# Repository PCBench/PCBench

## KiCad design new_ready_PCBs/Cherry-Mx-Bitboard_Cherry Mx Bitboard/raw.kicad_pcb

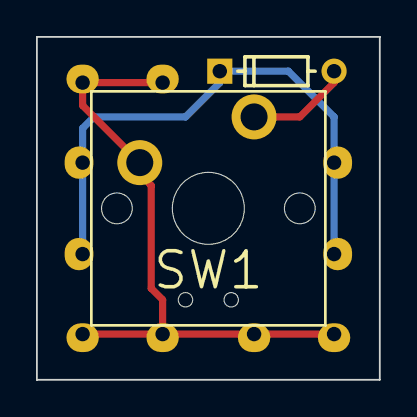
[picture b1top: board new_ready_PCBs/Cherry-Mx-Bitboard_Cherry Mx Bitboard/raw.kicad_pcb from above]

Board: 2 copper layers, 19.0 x 19.0 mm, 12 parts (1 on the bottom side), 3 nets.

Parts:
D1: D; diode
P11, P12, P13, P14, P15, P16, P21, P22, P23, P24: CONN_01X01; wirepad
SW1: SW_PUSH; switch

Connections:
/1: P11.1, P12.1, P13.1, P14.1, P15.1, P16.1, SW1.1
/2: D1.1, P21.1, P22.1, P23.1, P24.1
unnamed: D1.2, SW1.2

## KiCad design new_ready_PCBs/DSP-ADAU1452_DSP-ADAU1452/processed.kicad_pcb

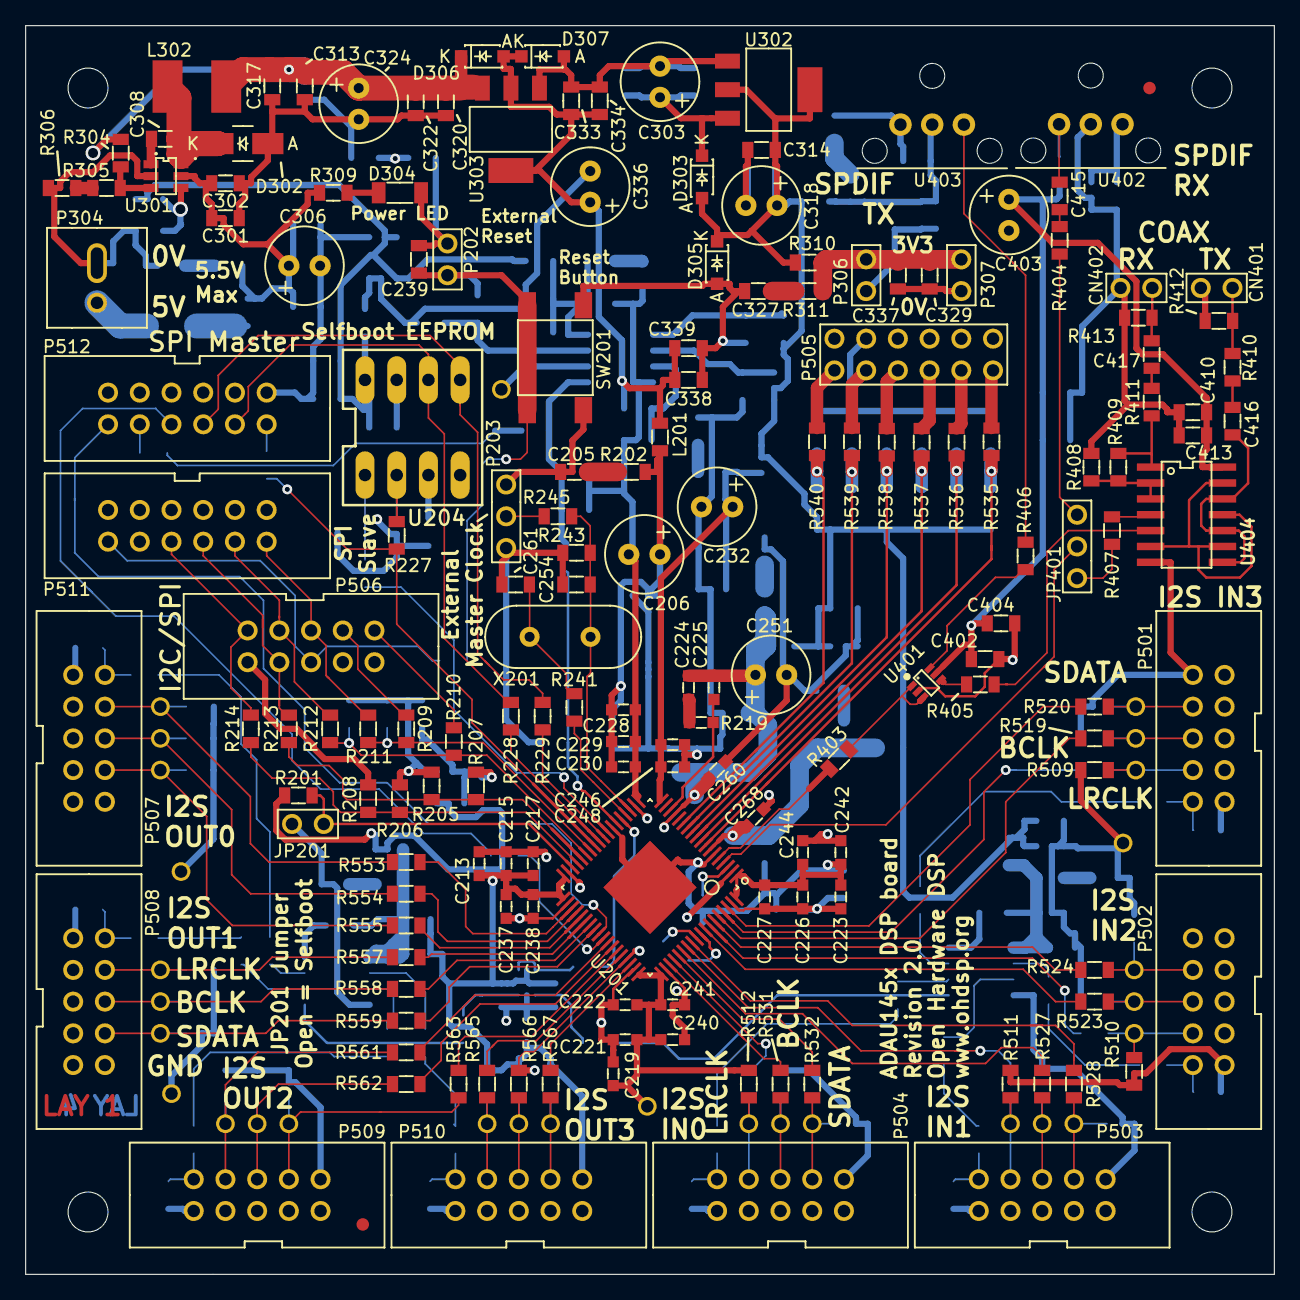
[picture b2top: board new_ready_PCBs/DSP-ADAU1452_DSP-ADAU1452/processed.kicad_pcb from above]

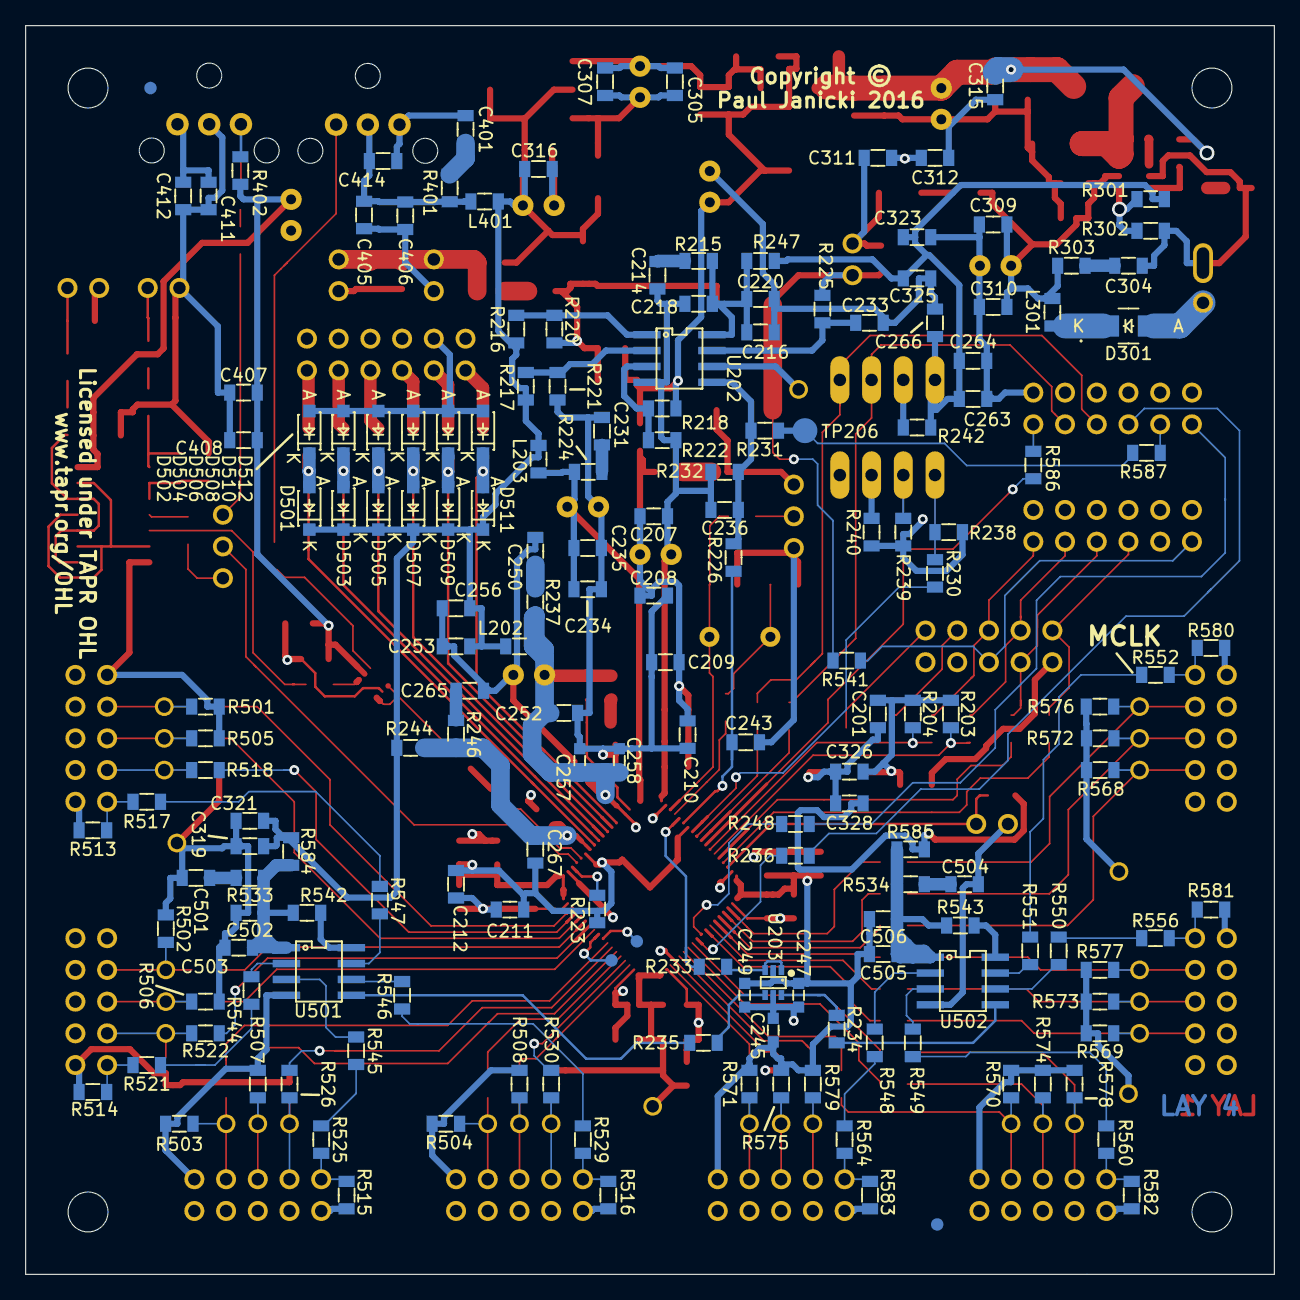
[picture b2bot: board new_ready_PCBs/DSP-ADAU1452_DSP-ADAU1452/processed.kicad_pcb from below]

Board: 4 copper layers, 100.0 x 100.0 mm, 377 parts (177 on the bottom side), 190 nets.

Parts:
C201, C208, C210, C212, C218, C233, C235, C236, C239, C243, C253, C264, C302, C307, C310, C314, C317, C319, C320, C323, C326, C329, C333, C338, C402, C406, C412, C413, C414, C416, C417, C503, C506: 100n; SMD-0805
C205, C214, C231, C250, C265, C304, C327, C401, C501, C504: 100p; SMD-0805
C206, C232, C251, C303, C306, C318, C324, C336, C403: 220u; CAP-TH-D6.3mmP2.5mm
C207, C234, C252, C267, C301, C305, C309, C313, C315, C316, C322, C334, C405, C502, C505: 22u; SMD-0805
C209, C211, C216, C256, C266, C321, C325, C328, C337, C339, C404, C410, C411: 10u; SMD-0805
C213, C219, C223, C228, C237, C240, C242, C245, C246, C257: 1u; SMD-0603
C215, C221, C226, C229, C238, C241, C244, C247, C248, C258, C268: 100n; SMD-0603
C217, C222, C227, C230, C249, C260: 10n; SMD-0603
C220, C263, C308, C415: 10n; SMD-0805
C224: 5n6; SMD-0603
C225: 150p; SMD-0603
C254, C261: 33p; SMD-0805
C311, C312, C407, C408: N/F; SMD-0805
CN401, CN402: COAX; CONN_SIL_2_1MM
D301, D302: B240A; DIODE-SMA
D303, D305, D306, D307, D501, D502, D503, D504, D505, D506, D507, D508, D509, D510, D511, D512: SS14L; DIODE-SOD-123
D304: Green LED 1206; SMD-1206
FID1, FID2, FID3, FID4: MNT_HOLE; FID-1MM-3MM
JP201: CONN_2x1; CONN_SIL_2_1MM
JP401: CONN_3x1; CONN_SIL_3_1MM
L201, L202, L203, L301, L401: 600R@100MHz; SMD-0805
L302: TYS50404R7N-10; IND-TYS5040-HS
MNT301, MNT302, MNT303, MNT304: MNT_HOLE; MNT_HOLE_3.2mm
P202, P306, P307: CONN_2x1; CONN_SIL_2_1MM
P203: CONN_3x1; CONN_SIL_3_1MM
P304: CONN_2x1; CONN-2WAY-2.54mm-3.81mm-SPACING
P501, P502, P503, P504, P506, P507, P508, P509, P510: CONN_02X05; CONN_DIL_2X5_BOX_1MM
P505: CONN_02X06; CONN_DIL_2X6_1MM
P511, P512: CONN_02X06; CONN_DIL_2X6_BOX_1MM
R201, R225, R542, R543: 1k; SMD-0805
R202, R215, R224, R237, R246, R303, R311, R401, R533, R534: 47; SMD-0805
R203, R204, R205, R206, R207, R208, R209, R210, R220, R239, R243, R245, R501, R502, R503, R504, R505, R506, R507, R508, R509, R510, R511, R512, R513, R514, R515, R516, R568, R569, R570, R571, R572, R573, R574, R575, R576, R577, R578, R579, R580, R581, R582, R583: N/F; SMD-0805
R211, R227, R228, R229, R230, R233, R234, R235, R236, R248, R403, R404, R405, R406, R407, R413, R544, R545, R546, R547, R548, R549, R550, R551, R553, R554, R555, R557, R558, R559, R561, R562, R563, R565, R566, R567: 75; SMD-0805
R212, R213, R214, R216, R223, R306, R517, R518, R519, R520, R521, R522, R523, R524, R525, R526, R527, R528, R529, R530, R531, R532, R541, R552, R556, R560, R564, R586, R587: 0; SMD-0805
R217: 12k; SMD-0805
R218: 3k3; SMD-0805
R219: 4k3; SMD-0603
R221: 3k; SMD-0805
R222: 3k6; SMD-0805
R226, R231, R241, R411: 100; SMD-0805
R232: 100k; SMD-0805
R238, R240, R242, R302, R402, R408, R409: 10k; SMD-0805
R244, R247, R310, R584, R585: 1; SMD-0805
R301: 16k; SMD-0805
R304: 24k; SMD-0805
R305: 15k; SMD-0805
R309: 470; SMD-0805
R410: 360; SMD-0805
R412: 91; SMD-0805
R535, R536, R537, R538, R539, R540: 4k7; SMD-0805
SW201: SWITCH; SW_TACT_SMD
TP201, TP501, TP502, TP503, TP504, TP505, TP506, TP507, TP508, TP509, TP510, TP511, TP512, TP513, TP514, TP515, TP516, TP517, TP518, TP519, TP520, TP521, TP522, TP523, TP524, TP525, TP526, TP527, TP528: PIN; TP-TH-1mm
TP204, TP205: PIN; TP-1mm
TP206: PIN; TP-2mm
U201: ADAU1452WBCPZ; IC-LFCSP72-HANDFIT
U202: ADM13307-5ARZ; IC_SOIC_8
U203: NC7WZ17P6X; IC-SC70-6
U204: 25AA1024; IC_DIP_8
U301: ADP2301AUJZ; IC-SOT23-6
U302: TLV1117LV33DCY; IC-SOT-223
U303: TLV1117LV12DCY; IC-SOT-223
U401: NC7WZ16P6X; IC-SC70-6
U402: IC-SPDIF-RX-OPTO; IC_SPDIF_OPTO
U403: IC-SPDIF-TX-OPTO; IC_SPDIF_OPTO
U404: 74HC04; IC_SOIC_14
U501, U502: NB3L553; IC_SOIC_8
X201: 24M576; XTAL_HC49_TH

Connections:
/ADAU1452/ADAU_SPDIF_RX: JP401.2, U201.4
/ADAU1452/ADAU_SPDIF_TX: R403.2, U201.5
/ADAU1452/ADCIN_BCLK0: R531.2, U201.57
/ADAU1452/ADCIN_BCLK1: R527.2, U201.60
/ADAU1452/ADCIN_BCLK2: R523.2, U201.65
/ADAU1452/ADCIN_BCLK3: R519.2, U201.68
/ADAU1452/ADCIN_LRCLK0: R530.2, U201.58
/ADAU1452/ADCIN_LRCLK1: R526.2, U201.61
/ADAU1452/ADCIN_LRCLK2: R522.2, U201.66
/ADAU1452/ADCIN_LRCLK3: R518.2, U201.69
/ADAU1452/ADCIN_SDATA0: R532.2, U201.59
/ADAU1452/ADCIN_SDATA1: R528.2, U201.62
/ADAU1452/ADCIN_SDATA2: R524.2, U201.67
/ADAU1452/ADCIN_SDATA3: R520.2, U201.70
/ADAU1452/AVDD: C267.1, C268.1, R244.1, R246.1, U201.7
/ADAU1452/DACOUT_BCLK0: R554.1, U201.40
/ADAU1452/DACOUT_BCLK1: R558.1, U201.43
/ADAU1452/DACOUT_BCLK2: R562.1, U201.48
/ADAU1452/DACOUT_BCLK3: R566.1, U201.51
/ADAU1452/DACOUT_LRCLK0: R553.1, U201.39
/ADAU1452/DACOUT_LRCLK1: R557.1, U201.42
/ADAU1452/DACOUT_LRCLK2: R561.1, U201.47
/ADAU1452/DACOUT_LRCLK3: R565.1, U201.50
/ADAU1452/DACOUT_SDATA0: R555.1, U201.41
/ADAU1452/DACOUT_SDATA1: R559.1, U201.44
/ADAU1452/DACOUT_SDATA2: R563.1, U201.49
/ADAU1452/DACOUT_SDATA3: R567.1, U201.52
/ADAU1452/DSP_RESET: C243.1, R226.1, U201.24
/ADAU1452/DVDD: C206.1, C207.1, C208.1, C209.1, C210.1, C211.1, C212.1, C213.1, C215.1, C217.1, C219.1, C221.1, C222.1, C223.1, C226.1, C227.1, C228.1, C229.1, C230.1, L201.2, R202.1, U201.20, U201.35, U201.53, U201.71
/ADAU1452/GLB_RESET: R231.1, R587.2, TP206.1
/ADAU1452/I2C_SCL: P506.1, R210.1
/ADAU1452/I2C_SDA: P506.3, R209.1
/ADAU1452/IOVDD: C232.1, C234.1, C235.1, C237.1, C238.1, C240.1, C241.1, C242.1, C244.1, C245.1, C246.1, C247.1, C248.1, C249.1, L203.2, R224.1, U201.2, U201.18, U201.38, U201.56, U203.5
/ADAU1452/MAN_RST_IN: C239.1, P202.1, R225.2, R541.2, SW201.1
/ADAU1452/MCLK: R235.1, U501.5
/ADAU1452/MCLK2: R234.1, U502.5
/ADAU1452/MCLK_ADAU: R233.2, U201.23
/ADAU1452/MISO/SDA: R204.2, R209.2, R211.2, U201.30
/ADAU1452/MOSI/ADDR1: R205.2, R207.2, R213.2, U201.32
/ADAU1452/M_SS: R230.2, R238.2, U204.1
/ADAU1452/PVDD: C224.1, C225.1, C251.1, C252.1, C257.1, C258.1, C260.1, L202.2, R237.1, U201.15
/ADAU1452/SCLK/SCL: R203.2, R210.2, R212.2, U201.31
/ADAU1452/SELFBOOT: JP201.1, R201.2, U201.34
/ADAU1452/SPI_MISO: P506.5, P511.2, R211.1
/ADAU1452/SPI_MOSI: P506.8, P511.6, R213.1
/ADAU1452/SPI_SCLK: P506.7, P511.4, R212.1
/ADAU1452/SPI_SS: P506.9, P511.8, R214.1
/ADAU1452/SS/ADDR0: R206.2, R208.2, R214.2, U201.33
/ADAU1452/XTALIN: C254.1, R243.1, R245.1, U201.21, X201.1
/ADAU1452/XTALOUT: R241.1, U201.22
/Connectors/AUXADCIN_1: D501.1, D502.2, R535.2, U201.8
/Connectors/AUXADCIN_2: D503.1, D504.2, R536.2, U201.9
/Connectors/AUXADCIN_3: D505.1, D506.2, R537.2, U201.10
/Connectors/AUXADCIN_4: D507.1, D508.2, R538.2, U201.11
/Connectors/AUXADCIN_5: D509.1, D510.2, R539.2, U201.12
/Connectors/AUXADCIN_6: D511.1, D512.2, R540.2, U201.13
/Connectors/I2C_RST: P506.6, P511.12, R541.1
/Connectors/MCLKA1: R529.2, R546.1
/Connectors/MCLKA2: R525.2, R545.1
/Connectors/MCLKA3: R521.2, R544.1
/Connectors/MCLKA4: R517.2, R547.1
/Connectors/MCLKB1: R551.1, R552.1
/Connectors/MCLKB2: R550.1, R556.1
/Connectors/MCLKB3: R549.1, R560.1
/Connectors/MCLKB4: R548.1, R564.1
/Connectors/M_MUTE: P512.12, R248.2
/Connectors/M_SPI_MISO: R227.1, R586.2, U201.29
/Connectors/M_SPI_MOSI: P512.6, R229.2, U204.5
/Connectors/M_SPI_SCLK: P512.4, R228.2, U204.6
/Connectors/M_SPI_SS: P512.8, R236.2
/Power Supply/2V1: C313.1, C315.1, C317.1, C320.1, C322.1, C324.1, D306.2, L302.2, R304.2, U303.3
GNDD: C201.2, C205.2, C206.2, C207.2, C208.2, C209.2, C210.2, C211.2, C212.2, C213.2, C214.2, C215.2, C216.2, C217.2, C218.2, C219.2, C220.2, C221.2, C222.2, C223.2, C226.2, C227.2, C228.2, C229.2, C230.2, C231.2, C232.2, C233.2, C234.2, C235.2, C236.2, C237.2, C238.2, C239.2, C240.2, C241.2, C242.2, C243.2, C244.2, C245.2, C246.2, C247.2, C248.2, C249.2, C250.2, C251.2, C252.2, C253.2, C254.2, C256.2, C257.2, C258.2, C260.2, C261.2, C263.2, C264.2, C265.2, C266.2, C267.2, C268.2, C301.1, C302.1, C303.2, C304.2, C305.2, C306.2, C307.2, C309.1, C310.1, C311.1, C312.1, C313.2, C314.2, C315.2, C316.2, C317.2, C318.2, C319.2, C320.2, C321.2, C322.2, C323.2, C324.2, C325.2, C326.2, C327.2, C328.2, C329.2, C333.2, C334.2, C336.2, C337.2, C338.2, C339.2, C401.2, C402.2, C403.2, C404.2, C405.2, C406.2, C407.2, C408.2, C410.2, C411.2, C412.2, C413.2, C414.2, C501.2, C502.2, C503.2, C504.2, C505.2, C506.2, CN401.2, CN402.2, D302.1, D304.2, D305.1, D307.1, D502.1, D504.1, D506.1, D508.1, D510.1, D512.1, JP201.2, P202.2, P203.1, P203.3, P304.2, P306.2, P307.2, P501.1, P501.3, P501.5, P501.7, P501.9, P501.10, P502.1, P502.3, P502.5, P502.7, P502.9, P502.10, P503.1, P503.3, P503.5, P503.7, P503.9, P503.10, P504.1, P504.3, P504.5, P504.7, P504.9, P504.10, P505.1, P505.3, P505.5, P505.7, P505.9, P505.11, P506.10, P507.1, P507.3, P507.5, P507.7, P507.9, P507.10, P508.1, P508.3, P508.5, P508.7, P508.9, P508.10, P509.1, P509.3, P509.5, P509.7, P509.9, P509.10, P510.1, P510.3, P510.5, P510.7, P510.9, P510.10, P511.1, P511.3, P511.5, P511.7, P511.9, P511.11, P512.1, P512.3, P512.5, P512.7, P512.9, P512.11, R207.1, R208.1, R220.1, R221.1, R222.1, R223.1, R232.1, R243.2, R302.1, R306.1, R408.1, R412.1, R413.1, R501.1, R502.1, R503.1, R504.1, R505.1, R506.1, R507.1, R508.1, R509.1, R510.1, R511.1, R512.1, R513.1, R514.1, R515.1, R516.1, R568.1, R569.1, R570.1, R571.1, R572.1, R573.1, R574.1, R575.1, R576.1, R577.1, R578.1, R579.1, R580.1, R581.1, R582.1, R583.1, SW201.2, TP513.1, TP514.1, TP515.1, TP516.1, U201.1, U201.6, U201.19, U201.25, U201.36, U201.37, U201.54, U201.55, U201.72, U201.EP1, U202.4, U203.2, U204.4, U301.2, U302.1, U303.1, U401.2, U402.2, U403.3, U404.7, U501.4, U502.4
unnamed: C205.1, R202.2
unnamed: C214.1, R215.2
unnamed: C216.1, C218.1, C220.1, R215.1, R247.1, U202.8
unnamed: C224.2, R219.1
unnamed: C225.2, R219.2, U201.16
unnamed: C231.1, R224.2
unnamed: C233.1, R225.1, U202.7
unnamed: C236.1, R226.2, R231.2, R232.2, U202.5
unnamed: C250.1, R237.2
unnamed: C261.1, R241.2, X201.2
unnamed: C265.1, R246.2
unnamed: C304.1, R303.2
unnamed: C308.1, U301.1
unnamed: C308.2, D302.2, L302.1, U301.6
unnamed: C327.1, R311.2
unnamed: C329.1, C337.1, P306.1, P307.1, R310.1, R311.1
unnamed: C401.1, R401.2
unnamed: C402.1, C403.1, C404.1, C405.1, C406.1, C407.1, C408.1, C410.1, C411.1, C412.1, C413.1, C414.1, L401.2, R401.1, R402.1, U401.5, U402.1, U403.2, U404.14
unnamed: C415.1, R404.2
unnamed: C415.2, R402.2, U402.3
unnamed: C416.1, R410.2
unnamed: C416.2, U404.8, U404.10, U404.12
unnamed: C417.1, R411.2
unnamed: C417.2, CN402.1, R413.2
unnamed: C501.1, R533.2
unnamed: C502.1, C503.1, R533.1, R542.2, R584.2, U501.1
unnamed: C504.1, R534.2
unnamed: C505.1, C506.1, R534.1, R543.2, R585.2, U502.1
unnamed: CN401.1, R410.1, R412.2
unnamed: D301.1, P304.1
unnamed: D301.2, L301.1
unnamed: D304.1, R309.2
unnamed: JP401.1, R404.1
unnamed: JP401.3, R407.2
unnamed: P203.2, R245.2
unnamed: P501.2, R513.2, R517.1
unnamed: P501.4, R509.2, R518.1, TP501.1
unnamed: P501.6, R505.2, R519.1, TP505.1
unnamed: P501.8, R501.2, R520.1, TP506.1
unnamed: P502.2, R514.2, R521.1
unnamed: P502.4, R510.2, R522.1, TP502.1
unnamed: P502.6, R506.2, R523.1, TP507.1
unnamed: P502.8, R502.2, R524.1, TP508.1
unnamed: P503.2, R515.2, R525.1
unnamed: P503.4, R511.2, R526.1, TP503.1
unnamed: P503.6, R507.2, R527.1, TP509.1
unnamed: P503.8, R503.2, R528.1, TP510.1
unnamed: P504.2, R516.2, R529.1
unnamed: P504.4, R512.2, R530.1, TP504.1
unnamed: P504.6, R508.2, R531.1, TP511.1
unnamed: P504.8, R504.2, R532.1, TP512.1
unnamed: P505.2, R535.1
unnamed: P505.4, R536.1
unnamed: P505.6, R537.1
unnamed: P505.8, R538.1
unnamed: P505.10, R539.1
unnamed: P505.12, R540.1
unnamed: P507.2, R552.2, R580.2
unnamed: P507.4, R553.2, R576.2, TP517.1
unnamed: P507.6, R554.2, R572.2, TP521.1
unnamed: P507.8, R555.2, R568.2, TP522.1
unnamed: P508.2, R556.2, R581.2
unnamed: P508.4, R557.2, R577.2, TP518.1
unnamed: P508.6, R558.2, R573.2, TP523.1
unnamed: P508.8, R559.2, R569.2, TP524.1
unnamed: P509.2, R560.2, R582.2
unnamed: P509.4, R561.2, R578.2, TP519.1
unnamed: P509.6, R562.2, R574.2, TP525.1
unnamed: P509.8, R563.2, R570.2, TP526.1
unnamed: P510.2, R564.2, R583.2
unnamed: P510.4, R565.2, R579.2, TP520.1
unnamed: P510.6, R566.2, R575.2, TP527.1
unnamed: P510.8, R567.2, R571.2, TP528.1
unnamed: P512.2, R586.1
unnamed: P512.10, R587.1
unnamed: R216.2, R220.2, U202.1
unnamed: R217.2, R221.2, U202.2
unnamed: R218.2, R222.2, U202.3
unnamed: R223.2, U201.3
unnamed: R227.2, R239.2, U204.2
unnamed: R228.1, U201.28
unnamed: R229.1, U201.27
unnamed: R230.1, U201.26
unnamed: R233.1, U203.1, U203.3
unnamed: R234.2, U203.6
unnamed: R235.2, U203.4
unnamed: R236.1, U201.46
unnamed: R240.2, U204.3
unnamed: R242.2, U204.7
unnamed: R248.1, U201.45
unnamed: R301.1, R302.2, U301.4
unnamed: R304.1, R305.2, U301.3
unnamed: R305.1, R306.2
unnamed: R403.1, U401.1, U401.3
unnamed: R405.1, U404.5
unnamed: R405.2, U401.4
unnamed: R406.1, U401.6
unnamed: R406.2, U403.1
unnamed: R407.1, U404.4
unnamed: R408.2, R409.1, U404.2, U404.3
unnamed: R409.2, R411.1, U404.1
unnamed: R542.1, U501.8
unnamed: R543.1, U502.8
unnamed: R544.2, U501.2
unnamed: R545.2, U501.3
unnamed: R546.2, U501.6
unnamed: R547.2, U501.7
unnamed: R548.2, U502.2
unnamed: R549.2, U502.3
unnamed: R550.2, U502.6
unnamed: R551.2, U502.7
unnamed: TP201.1, U202.6
unnamed: TP204.1, U201.64
unnamed: TP205.1, U201.63
unnamed: U404.6, U404.9, U404.11, U404.13
VAA: C201.1, C253.1, C256.1, C263.1, C264.1, C266.1, C314.1, C316.1, C318.1, C319.1, C321.1, C323.1, C325.1, C326.1, C328.1, D303.1, D305.2, D501.2, D503.2, D505.2, D507.2, D509.2, D511.2, L202.1, L203.1, L401.1, R201.1, R203.1, R204.1, R205.1, R206.1, R216.1, R217.1, R238.1, R239.1, R240.1, R242.1, R244.2, R247.2, R301.2, R310.2, R584.1, R585.1, U204.8, U302.2
VCC: C301.2, C302.2, C303.1, C305.1, C306.1, C307.1, C309.2, C310.2, C311.2, C312.2, D303.2, L301.2, R303.1, R309.1, U301.5, U302.3
VDD: C333.1, C334.1, C336.1, C338.1, C339.1, D306.1, D307.2, L201.1, R218.1, U303.2

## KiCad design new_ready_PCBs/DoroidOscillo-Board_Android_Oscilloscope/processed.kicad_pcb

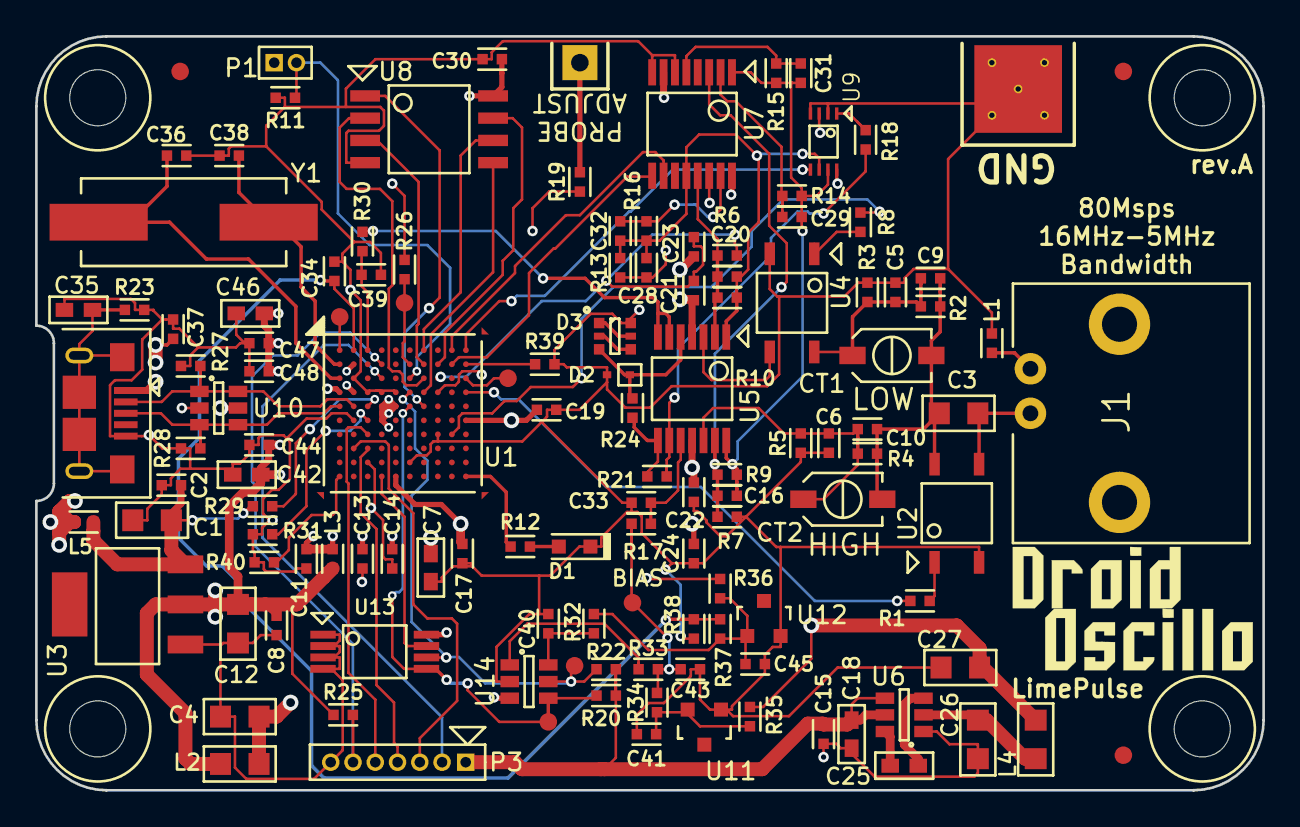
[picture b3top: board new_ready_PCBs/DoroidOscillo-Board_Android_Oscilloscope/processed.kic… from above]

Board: 4 copper layers, 70.0 x 43.0 mm, 132 parts (0 on the bottom side), 77 nets.

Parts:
C1, C4, C12, C26, C27: 22u 6.3V; SMD2012
C2, C8, C11, C14, C15, C17, C19, C23, C24, C30, C33, C37, C41, C43, C44, C45, C47: 0.1u; SMD1005
C3: 47n 100V; SMD2012
C5, C32: 4.7p; SMD1005
C6: 120p; SMD1005
C7, C18, C42, C46: 10u 6.3V; SMD1608
C9, C10, C39: NM; SMD1005
C13, C48: 22n; SMD1005
C16, C20: 2.2p; SMD1005
C21, C22, C34, C40: 1u; SMD1005
C25: 4.7u 6.3V; SMD1608
C28: 15p; SMD1005
C29: 3.3p; SMD1005
C31: 10p; SMD1005
C35: 4.7n 100V; SMD1608
C36, C38: 18p; SMD1005
CT1: TZC3R100A110 3p-10p; MURATA_TZC3
CT2: TZC3Z030A110R00 1.4p-3p; MURATA_TZC3
D1: APT1608EC; SMD1608_DIODE
D2: RB521S30T5G; SOD-523
D3: BAS16VY; SOT-363
FID1: Fiducial_C; Fiducial_1mm
FID2: Fiducial_A; Fiducial_1mm
FID3: Fiducial_B; Fiducial_1mm
HOLE3MM_NC, HOLE3MM_NC_2, HOLE3MM_NC_3, HOLE3MM_NC_4: VAL**; HOLE3MM_NC
J1: BNC; BNC-R
L1, L5: BLM15AG121SN1; SMD1005
L2, L4: LBR2012T202K; SMD2012
L3: BLM15AG601SN1; SMD1005
P1: USB_BOOT; PIN_HEADER_2_1.27mm
P2: FCI_10118193-0001LF; 10118193-0001LF
P3: JTAG; PIN_HEADER_7_1.27pitch
R1, R8, R11, R36, R39, R40: 2.2k 5%; SMD1005
R2: 1100k 1%; SMD1005
R3: 910k 1%; SMD1005
R4: 1.96M 1%; SMD1005
R5: 36k 1%; SMD1005
R6, R7: 3k 1%; SMD1005
R9, R10: 27k 1%; SMD1005
R12: 10k 5%; SMD1005
R13: 3.3k 1%; SMD1005
R14: 22k 1%; SMD1005
R15: 5.6k 1%; SMD1005
R16: 13.3k 1%; SMD1005
R17, R32: 4.7k 5%; SMD1005
R18: 910 1%; SMD1005
R19, R29: 100 5%; SMD1005
R20, R22, R25, R26: 4.7k; SMD1005
R21: 1k 1%; SMD1005
R23, R27, R28: 1M 5%; SMD1005
R24: 680 1%; SMD1005
R30: 0; SMD1005
R31: 12k 1%; SMD1005
R33: 2k 1%; SMD1005
R34: 8.2k 1%; SMD1005
R35, R38: 1.5k 1%; SMD1005
R37: 2.2k 1%; SMD1005
TP1: SCL; TestPad
TP2: SDA; TestPad
TP3: RST; TestPad
U1: LPC4370FET100; TFBGA100_MYREFLOW
U2, U4: CPC1017N
U3: AMS1117-3.3; SOT-223
U5: OPA4354AIPWR; TSSOP-14_4.4x5mm_Pitch0.65mm
U6: LM2664; SOT-23-6
U7: 74HC4052PW; TSSOP-16_4.4x5mm_Pitch0.65mm
U8: W25Q80BVSSIG; SOIJ-8_5.3x5.3mm_Pitch1.27mm
U9: TC7W53FK; SSOP8_P0.5W2.3
U10: USBLC6-2SC6; SOT-23-6
U11, U12: LM385M3-1.2/NOPB; SOT-23
U13: AT24C02C-XHM-T; TSSOP-8_4.4x3mm_Pitch0.65mm
U14: MCP4726A0T-E/CH; SOT-23-6
W1: ISP; TestPad
W2: PROBE_COMP_HOLE
W3: ADC1; TestPad
W4: PROBE_GND_PAD; Probe-ADJ-GND
W5: TP_BIAS; TestPad
Y1: ABLS-12.000MHZ-B4-T; Crystal_HC49-SD_SMD

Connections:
/USB_D+: P2.3, R28.1, U1.E1, U10.3, U10.4
/USB_D-: P2.2, R27.1, U1.E2, U10.1, U10.6
/USB_VBUS: R29.1, U1.E3
ADCHS_VNEG: C39.1, R30.2, U1.A3
ADCHS_VPOS0: C34.1, R37.2, R38.1, U1.A2
BIAS: C43.2, R17.1, R33.2, R34.1, W5.1
BOOT1: R40.1, U1.K1
BOOT2: P1.2, R11.1, U1.C6
BOOT3: R39.1, U1.B10
BOOT_ISP: U1.C10, W1.1
DAC_OUT: R33.1, U14.1
DAC_VREF: C45.1, R32.1, R36.2, R37.1, U12.1
DC_SW: R1.1, U1.D10
EEPROM_WP: U1.K4, U13.7
GND: C1.2, C2.2, C4.2, C5.2, C6.2, C7.2, C8.2, C11.2, C12.2, C13.2, C14.2, C15.2, C17.2, C18.2, C19.2, C21.2, C22.1, C23.2, C24.1, C26.2, C27.2, C30.2, C33.2, C34.2, C35.2, C36.1, C37.2, C38.1, C39.2, C40.1, C41.2, C42.2, C43.1, C44.2, C45.2, C46.2, C47.2, C48.2, D1.1, D2.2, D3.6, L1.2, P2.5, P3.7, R3.1, R5.2, R6.2, R7.2, R11.2, R23.2, R27.2, R28.2, R31.2, R38.2, R39.2, R40.2, U1.C2, U1.C8, U1.D3, U1.D4, U1.D5, U1.F2, U1.G8, U1.J3, U1.J6, U2.2, U3.1, U4.2, U6.1, U7.6, U7.8, U8.4, U9.2, U9.4, U10.2, U11.1, U12.2, U13.1, U13.2, U13.3, U13.4, U14.2, W4.1
I2C_SCL: R22.2, TP1.1, U1.D6, U13.6, U14.5
I2C_SDA: R20.2, TP2.1, U1.E6, U13.5, U14.4
JTAG_RESET: P3.6, R25.2, U1.B4
JTAG_TCK: P3.3, U1.H2
JTAG_TDI: P3.5, U1.G3
JTAG_TDO: P3.4, U1.H3
JTAG_TMS: P3.2, U1.C4
LED0: R12.1, U1.K10
MUX0-S0: U1.A9, U7.10
MUX0-S1: U1.B9, U7.9
MUX1-A: U1.A10, U9.5
unnamed: C3.1, J1.C, U2.3
unnamed: C5.1, C9.2, CT1.2, R2.1, R3.2, U4.4
unnamed: C3.2, C9.1, C10.1, CT1.1, CT2.1, R2.2, R4.1, U2.4
unnamed: C6.1, C10.2, CT2.2, R4.2, R5.1, U5.12
unnamed: C7.1, C11.1, C13.1, C14.1, L3.2, U1.E4, U1.E5, U1.F4
unnamed: C16.1, C29.2, C31.2, R9.2, R14.2, R15.2, U5.14, U7.1, U9.7
unnamed: C16.2, R7.1, R9.1, U5.13, U7.3
unnamed: C20.1, R6.1, R10.2, U5.2, U7.13
unnamed: C20.2, C28.1, C32.1, R10.1, R13.1, R16.1, U5.1, U7.12, U9.6
unnamed: C25.1, U6.6
unnamed: C25.2, U6.3
unnamed: C26.1, L4.1, U6.2
unnamed: C28.2, R13.2, U7.14
unnamed: C29.1, R14.1, U7.2
unnamed: C31.1, R15.1, U7.5
unnamed: C32.2, R16.2, U7.15
unnamed: C33.1, R17.2, U5.10
unnamed: C35.1, P2.S1, P2.S2, P2.S3, P2.S4, P2.S5, P2.S6, R23.1
unnamed: C36.2, U1.C1, Y1.1
unnamed: C37.1, L5.1, P2.1, U10.5
unnamed: C38.2, U1.B1, Y1.2
unnamed: C40.2, R32.2, U14.6
unnamed: C41.1, R34.2, R35.1, U11.2
unnamed: D1.2, R12.2
unnamed: D2.1, D3.3, R24.2, U5.5
unnamed: D3.1, D3.5
unnamed: D3.2, D3.4
unnamed: J1.S, L1.1
unnamed: R1.2, U2.1
unnamed: R8.1, U4.1
unnamed: R18.1, R21.2, U5.9
unnamed: R18.2, U9.1
unnamed: R19.1, W2.1
unnamed: R21.1, R24.1, U5.8
unnamed: R26.2, TP3.1, U1.B6
unnamed: R30.1, U5.6, U5.7
unnamed: R31.1, U1.F3
unnamed: U1.A1, W3.1
unnamed: U4.3, U5.3
OP_SW: R8.2, U1.G9
PROBE_COMP: R19.2, U1.D8
SPIFI_CS: U1.E7, U8.1
SPIFI_MISO: U1.C7, U8.2
SPIFI_MOSI: U1.D7, U8.5
SPIFI_SCK: U1.A7, U8.6
SPIFI_SIO2: U1.B7, U8.3
SPIFI_SIO3: U1.B8, U8.7
VBUS: C1.1, C2.1, L5.2, R29.2, U3.3
alt_3.3VD: C8.1, C12.1, C15.1, C17.1, C18.1, C19.1, C30.1, C42.1, C44.1, C46.1, C47.1, C48.1, L2.1, L3.1, P1.1, P3.1, R20.1, R22.1, R25.1, R26.1, U1.B2, U1.D1, U1.D2, U1.F10, U1.K5, U3.2, U6.4, U6.5, U8.8, U13.8
alt_VAA+: C4.1, C21.1, C23.1, L2.2, R36.1, U5.4, U7.16, U9.8, U14.3
alt_VAA-: C22.2, C24.2, C27.1, L4.2, R35.2, U5.11, U7.7, U9.3

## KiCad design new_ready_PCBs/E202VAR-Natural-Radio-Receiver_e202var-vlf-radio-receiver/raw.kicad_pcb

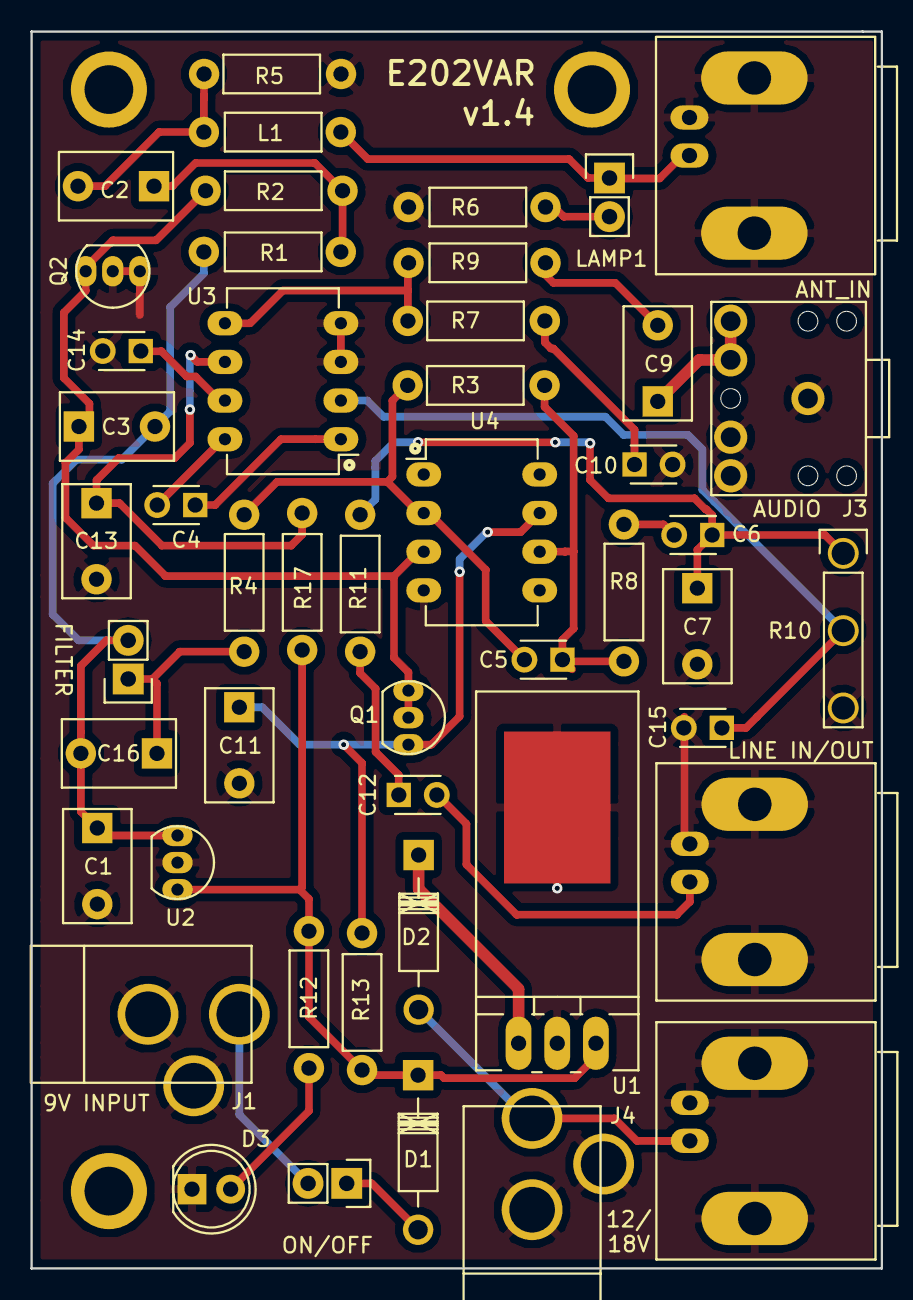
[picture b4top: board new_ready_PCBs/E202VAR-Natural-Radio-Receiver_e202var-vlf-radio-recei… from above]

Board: 2 copper layers, 55.9 x 81.3 mm, 51 parts (0 on the bottom side), 30 nets.

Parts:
BNC1: 12/18V; CONN-BNC-TECONN-1-1634612-0
BNC2: ANT IN; CONN-BNC-TECONN-1-1634612-0
BNC3: LINE IN/OUT; CONN-BNC-TECONN-1-1634612-0
C1: 33nF; CAP-DISC-D7.5MM-P5MM
C2, C11: 100nF; CAP-DISC-D7.5MM-P5MM
C3: 8.2pF; CAP-DISC-D7.5MM-P5MM
C4, C6, C12: 10uF; CAP-DISC-D3MM-P2.5MM
C5: 150pF; CAP-DISC-D3MM-P2.5MM
C7, C16: 4.7nF; CAP-DISC-D7.5MM-P5MM
C9, C13: 100uF; CAP-DISC-D7.5MM-P5MM
C10: 10nF; CAP-DISC-D3MM-P2.5MM
C14, C15: 22nF; CAP-DISC-D3MM-P2.5MM
D1, D2: 1N4001; DIODE-DO-41
D3: BLUE; LED-D5MM-2PIN
H1, H2, H3: HOLE-PLATED-3.2MM
J1: 9V; CONN-BARREL-JACK-2.5x5.5MM-TH
J2: ON/OFF; CONN-ONSHORE-SCREW-GREEN-2PIN-TH
J3: HEADPHONES; SJ1-3523N
J4: 12V/18V; CONN-BARREL-JACK-2.5x5.5MM-TH
J5: FILTER; CONN-ONSHORE-SCREW-GREEN-2PIN-TH
L1: 3.3UH; RES-CARBONFILM-7MM
LAMP1: NEON; CONN-HEADER-STRAIGHT-P2.54MM-1x02
Q1, Q2: BC547; TO-92-INLINE-NARROW-OVAL
R1, R5: 10M; RES-CARBONFILM-7MM
R2, R3, R6: 100K; RES-CARBONFILM-7MM
R4: 3.3k; RES-CARBONFILM-7MM
R7: 10; RES-CARBONFILM-7MM
R8: 10K; RES-CARBONFILM-7MM
R9, R17: 33; RES-CARBONFILM-7MM
R10: 10K; RES-TRIMPOT-TTELEC-P160-TH
R11: 4.7K; RES-CARBONFILM-7MM
R12: 2.2K; RES-CARBONFILM-7MM
R13: 1K; RES-CARBONFILM-7MM
U1: MC7809; TO-220-NEUTRAL123-HORZ-LONGPADS
U2: TLE2426; TO-92-INLINE-NARROW-OVAL
U3: NJM386; DIP-8-W7.62MM-LONGPADS
U4: TL081CP; DIP-8-W7.62MM-LONGPADS

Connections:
+2V: C1.1, C3.2, C16.2, J5.2, R1.2, U2.1
+9V: D1.1, R12.1, R13.1, R17.1, U1.3, U2.3
GND: BNC1.2, BNC2.2, BNC3.2, C1.2, C7.2, C10.2, C11.2, C13.2, C14.2, C15.2, D3.1, J1.2, J1.3, J3.3, J3.4, J3.5, J4.2, J4.3, Q2.1, Q2.2, R5.2, R6.2, R10.3, U1.2, U2.2, U3.3, U3.4, U4.4
unnamed: BNC1.1, D2.2, J4.1
unnamed: BNC2.1, L1.1, LAMP1.1
unnamed: BNC3.1, C12.2
unnamed: C2.1, R1.1, R2.2
unnamed: C2.2, L1.2, R5.1
unnamed: C3.1, Q1.1, Q1.2, Q2.3, R2.1, U4.3
unnamed: C4.1, U3.1
unnamed: C4.2, U3.8
unnamed: C5.1, R3.2, R8.2, U4.6
unnamed: C5.2, R3.1, R4.1, U4.2
unnamed: C6.1, C7.1, R10.1, R11.2
unnamed: C6.2, R8.1
unnamed: C9.1, J3.1, J3.2
unnamed: C9.2, R9.1
unnamed: C10.1, R7.2
unnamed: C11.1, Q1.3, R13.2, U4.7
unnamed: C12.1, R11.1
unnamed: C13.1, R17.2, U3.6
unnamed: C14.1, U3.7
unnamed: C15.1, R10.2, U3.2
unnamed: C16.1, J5.1, R4.2
unnamed: D1.2, J2.1
unnamed: D2.1, U1.1
unnamed: D3.2, R12.2
unnamed: J1.1, J2.2
unnamed: LAMP1.2, R6.1
unnamed: R7.1, R9.2, U3.5

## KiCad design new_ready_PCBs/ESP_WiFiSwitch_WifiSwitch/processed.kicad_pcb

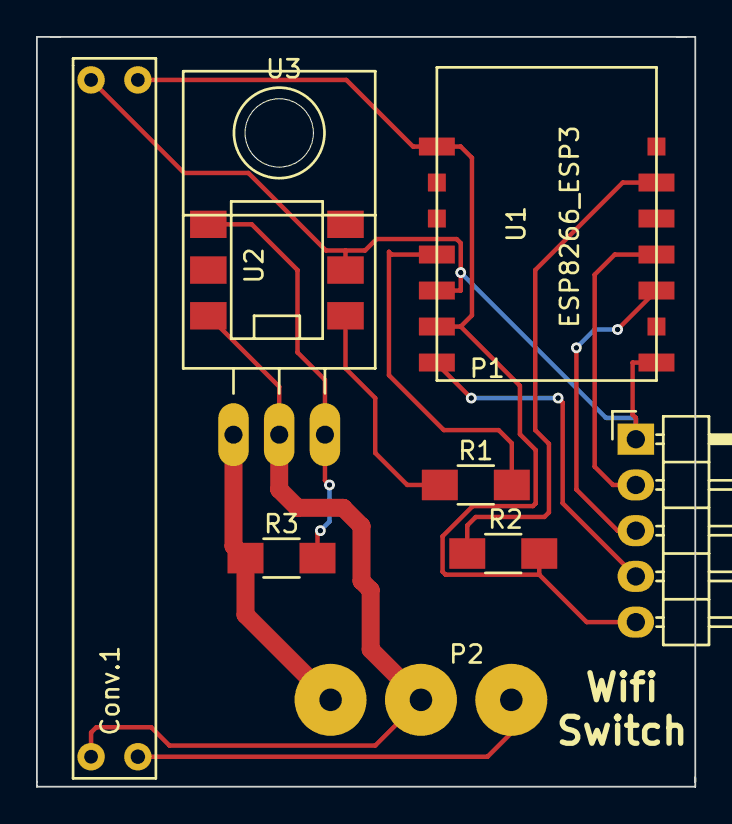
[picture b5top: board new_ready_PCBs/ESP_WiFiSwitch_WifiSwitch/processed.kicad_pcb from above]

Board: 2 copper layers, 36.6 x 41.7 mm, 9 parts (0 on the bottom side), 12 nets.

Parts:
Conv.1: AC to DC convertor 3V3; AC_DC_Conv
P1: CONN_01X05; Pin_Header_Angled_1x05
P2: CONN_01X03; WirePad_3x-5mmDrill
R1: 220R; R_1206_HandSoldering
R2: 4K7; R_1206_HandSoldering
R3: 330R; R_1206_HandSoldering
U1: ESP8266_ESP3; ESP8266-ESP-03
U2: MOC3031S; DIP-6_SMD
U3: TRIAC; TO-220_Neutral123_Horizontal_LargePads

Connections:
+3V3: Conv.1.1, P1.5, R2.2, U1.8, U1.13
GND: Conv.1.2, P1.1, U1.1, U1.12, U2.2
unnamed: Conv.1.3, P2.3
unnamed: Conv.1.4, P2.2, U2.6, U3.2
unnamed: P1.2, U1.4
unnamed: P1.3, U1.3
unnamed: P1.4, U1.14
unnamed: P2.1, R3.2, U3.1
unnamed: R1.1, U2.1
unnamed: R1.2, U1.11
unnamed: R2.1, U1.6
unnamed: R3.1, U2.4, U3.3

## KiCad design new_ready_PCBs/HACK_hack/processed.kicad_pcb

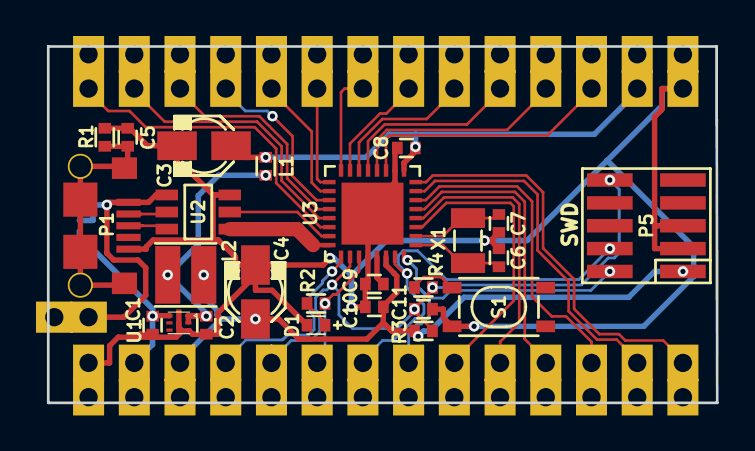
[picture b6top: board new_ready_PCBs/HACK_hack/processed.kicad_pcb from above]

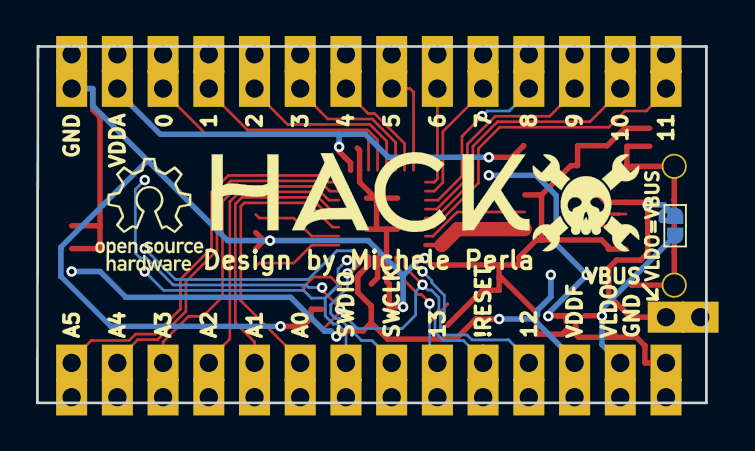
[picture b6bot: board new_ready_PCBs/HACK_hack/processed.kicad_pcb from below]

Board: 2 copper layers, 37.2 x 19.8 mm, 32 parts (6 on the bottom side), 39 nets.

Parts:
C1, C2: 2.2uF; C_0603
C3, C4: 10uF; c_elec_3x5.3
C5: 4.7nF; C_0603
C6, C7: 10pF; C_0603
C8, C9, C10, C11: 100nF; C_0603
D1: RED; LED_0603
JP1: Jumper_NO_Small; SMD_Jumper
L1: BLM18EG221; L_0603
L2: 10uH; ELLVFG
LOGO1: OSHW; OSHW-LOGO
LOGO2: HACKADAY; HACKADAY-LOGO
LOGO3: HACK; HACK-small
P1: USB_micro; 10118193-0001LF
P2, P3: CONN_01X14; Pin_Castellated_1x14
P4: CONN_01X01; Pin_Castellated_1x01
P5: CONN_SWD; Cortex_Debug_Connector_50mils
R1: 1M; R_0603
R2, R4: 330; R_0603
R3: 10k; R_0603
S1: RST; SPST-PTS_810
U1: MIC5528; DFN-6-1EP_1.2x1.2mm_Pitch0.4mm
U2: STF202; TSOP-6
U3: ATSAMD21E; QFN-32-1EP_5x5mm_Pitch0.5mm
X1: ABS07; xtal_3.2x1.5mm

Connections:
!RESET: C11.1, P2.5, P5.10, R3.1, R4.1, U3.26
/VDDCORE: C9.1, U3.29
/shield: C5.2, P1.6, R1.2
GND: C1.2, C2.2, C3.2, C4.2, C5.1, C6.2, C7.2, C8.2, C9.2, C10.2, C11.2, D1.2, P1.5, P2.1, P3.14, P5.3, P5.5, R1.1, S1.1, U1.3, U1.7, U2.6, U3.10, U3.28, U3.33
unnamed: D1.1, R2.2
unnamed: P1.2, U2.2
unnamed: P1.3, U2.3
unnamed: R4.2, S1.3
PA02/A0: P2.9, U3.3
PA03/A1: P2.10, U3.4
PA04/A2: P2.11, U3.5
PA05/A3: P2.12, U3.6
PA06/A4: P2.13, U3.7
PA07/A5: P2.14, U3.8
PA08/0: P3.12, U3.11
PA09/1: P3.11, U3.12
PA10/2: P3.10, U3.13
PA11/3: P3.9, U3.14
PA14/4: P3.8, U3.15
PA15/5: P3.7, U3.16
PA16/6: P3.6, U3.17
PA17/7: P3.5, U3.18
PA18/8: P3.4, U3.19
PA19/9: P3.3, U3.20
PA22/10: P3.2, U3.21
PA23/11: P3.1, U3.22
PA27/12: P2.4, U3.25
PA28/13: P2.6, R2.1, U3.27
PA30/SWCLK: P2.7, P5.4, U3.31
PA31/SWDIO: P2.8, P5.2, U3.32
USB-D+: U2.4, U3.24
USB-D-: U2.5, U3.23
VBUS: JP1.1, P1.1, P4.1, U2.1
VDD: C2.1, L1.1, L2.1, U1.1, U1.2
VDDANA: C3.1, C8.1, L1.2, P3.13, U3.9
VDDF: C4.1, C10.1, L2.2, P2.3, P5.1, R3.2, U3.30
VLDO: C1.1, JP1.2, P2.2, U1.6
XIN32: C6.1, U3.1, X1.1
XOUT32: C7.1, U3.2, X1.2

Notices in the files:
new_ready_PCBs/DSP-ADAU1452_DSP-ADAU1452/processed.kicad_pcb:
Licensed under the TAPR Open Hardware License (www.tapr.org/OHL). This documentation
Copyright Paul Janicki 2016
Copyright ©
Licensed under TAPR OHL
new_ready_PCBs/E202VAR-Natural-Radio-Receiver_e202var-vlf-radio-receiver/raw.kicad_pcb:
CERN Open Hardware License v1.2
